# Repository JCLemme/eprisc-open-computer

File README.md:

# epRISC Open Computer
An open-source computer

# **THIS REPO IS DEPRECATED - check out the "eprisc", "snag", "spasm", and "flail" repositories instead**

---

## Building things
Right now, the system testbench and the assembler can be compiled. Just run the provided Makefiles in their respective directories.

To build the system testbench, you'll need make, Icarus Verilog, and ideally some sort of waveform viewer (like GTKWave). The testbench emulates all of the system's I/O devices, but they aren't connected to anything, so you'll have to read the output waveforms yourself and determine if they're correct or not for debugging. Another thing to pay attention to is the length of time the testbench runs for; running the emulation long enough to catch rare problems might generate VCD files of several hundred megabytes.

To build spasm, you'll need g++, make, and libboost. Everything's been updated for the v5 ISA.

## Developing software
You can use spasm and the system testbench to develop software for the epRISC system. Documentation isn't complete for the new parts of the assembler, but you can use the code in the software/rom/ directory as a starting point. The full list of assembly instructions are in the .cpu file in the software/toolchain/spasm/ directory. 

The assembler can generate binaries in big-endian format and Verilog arrays. Run spasm with the -t flag, replace the contents of the array in the firmware/core/rom_v1r0.v file with the output file generated by spasm, and make the system testbench as directed above. 

## Running on hardware
A Quartus project is provided in the firmware/core directory to run the CPU and its peripherals on an Altera MAX 10 FPGA. You should be able, with little modification, to get the project to synthesize to another Altera FPGA or to another manufacturer's FPGA.

As of 04-05-2017, the computer is running successfully on its development board. If you're interested in running the system on your hardware, please contact me.

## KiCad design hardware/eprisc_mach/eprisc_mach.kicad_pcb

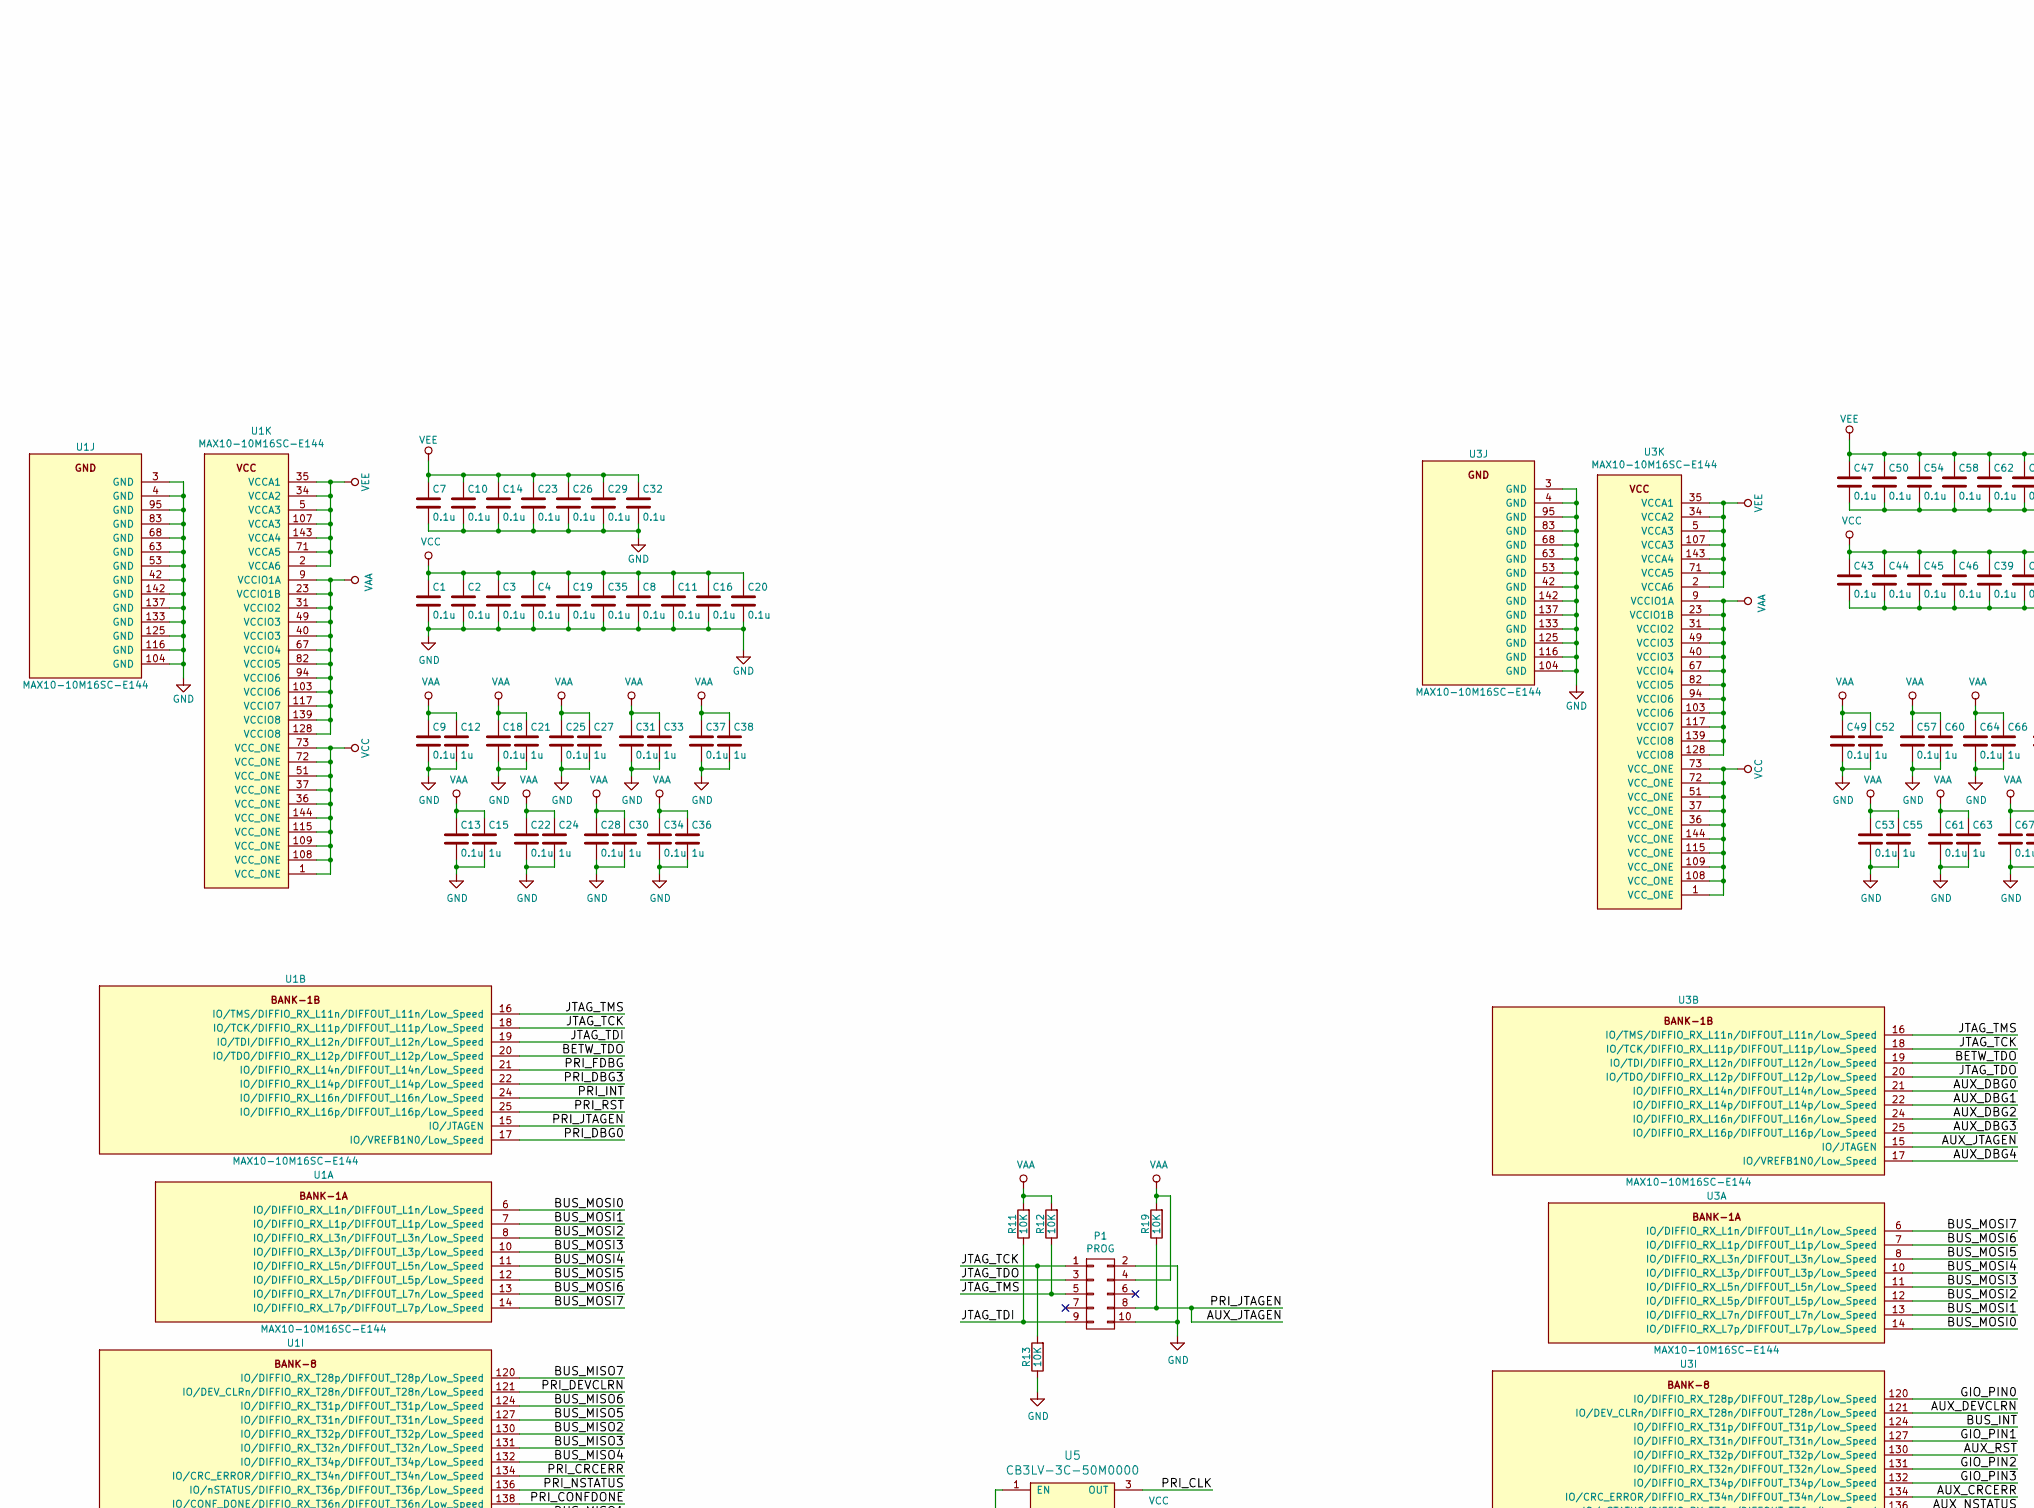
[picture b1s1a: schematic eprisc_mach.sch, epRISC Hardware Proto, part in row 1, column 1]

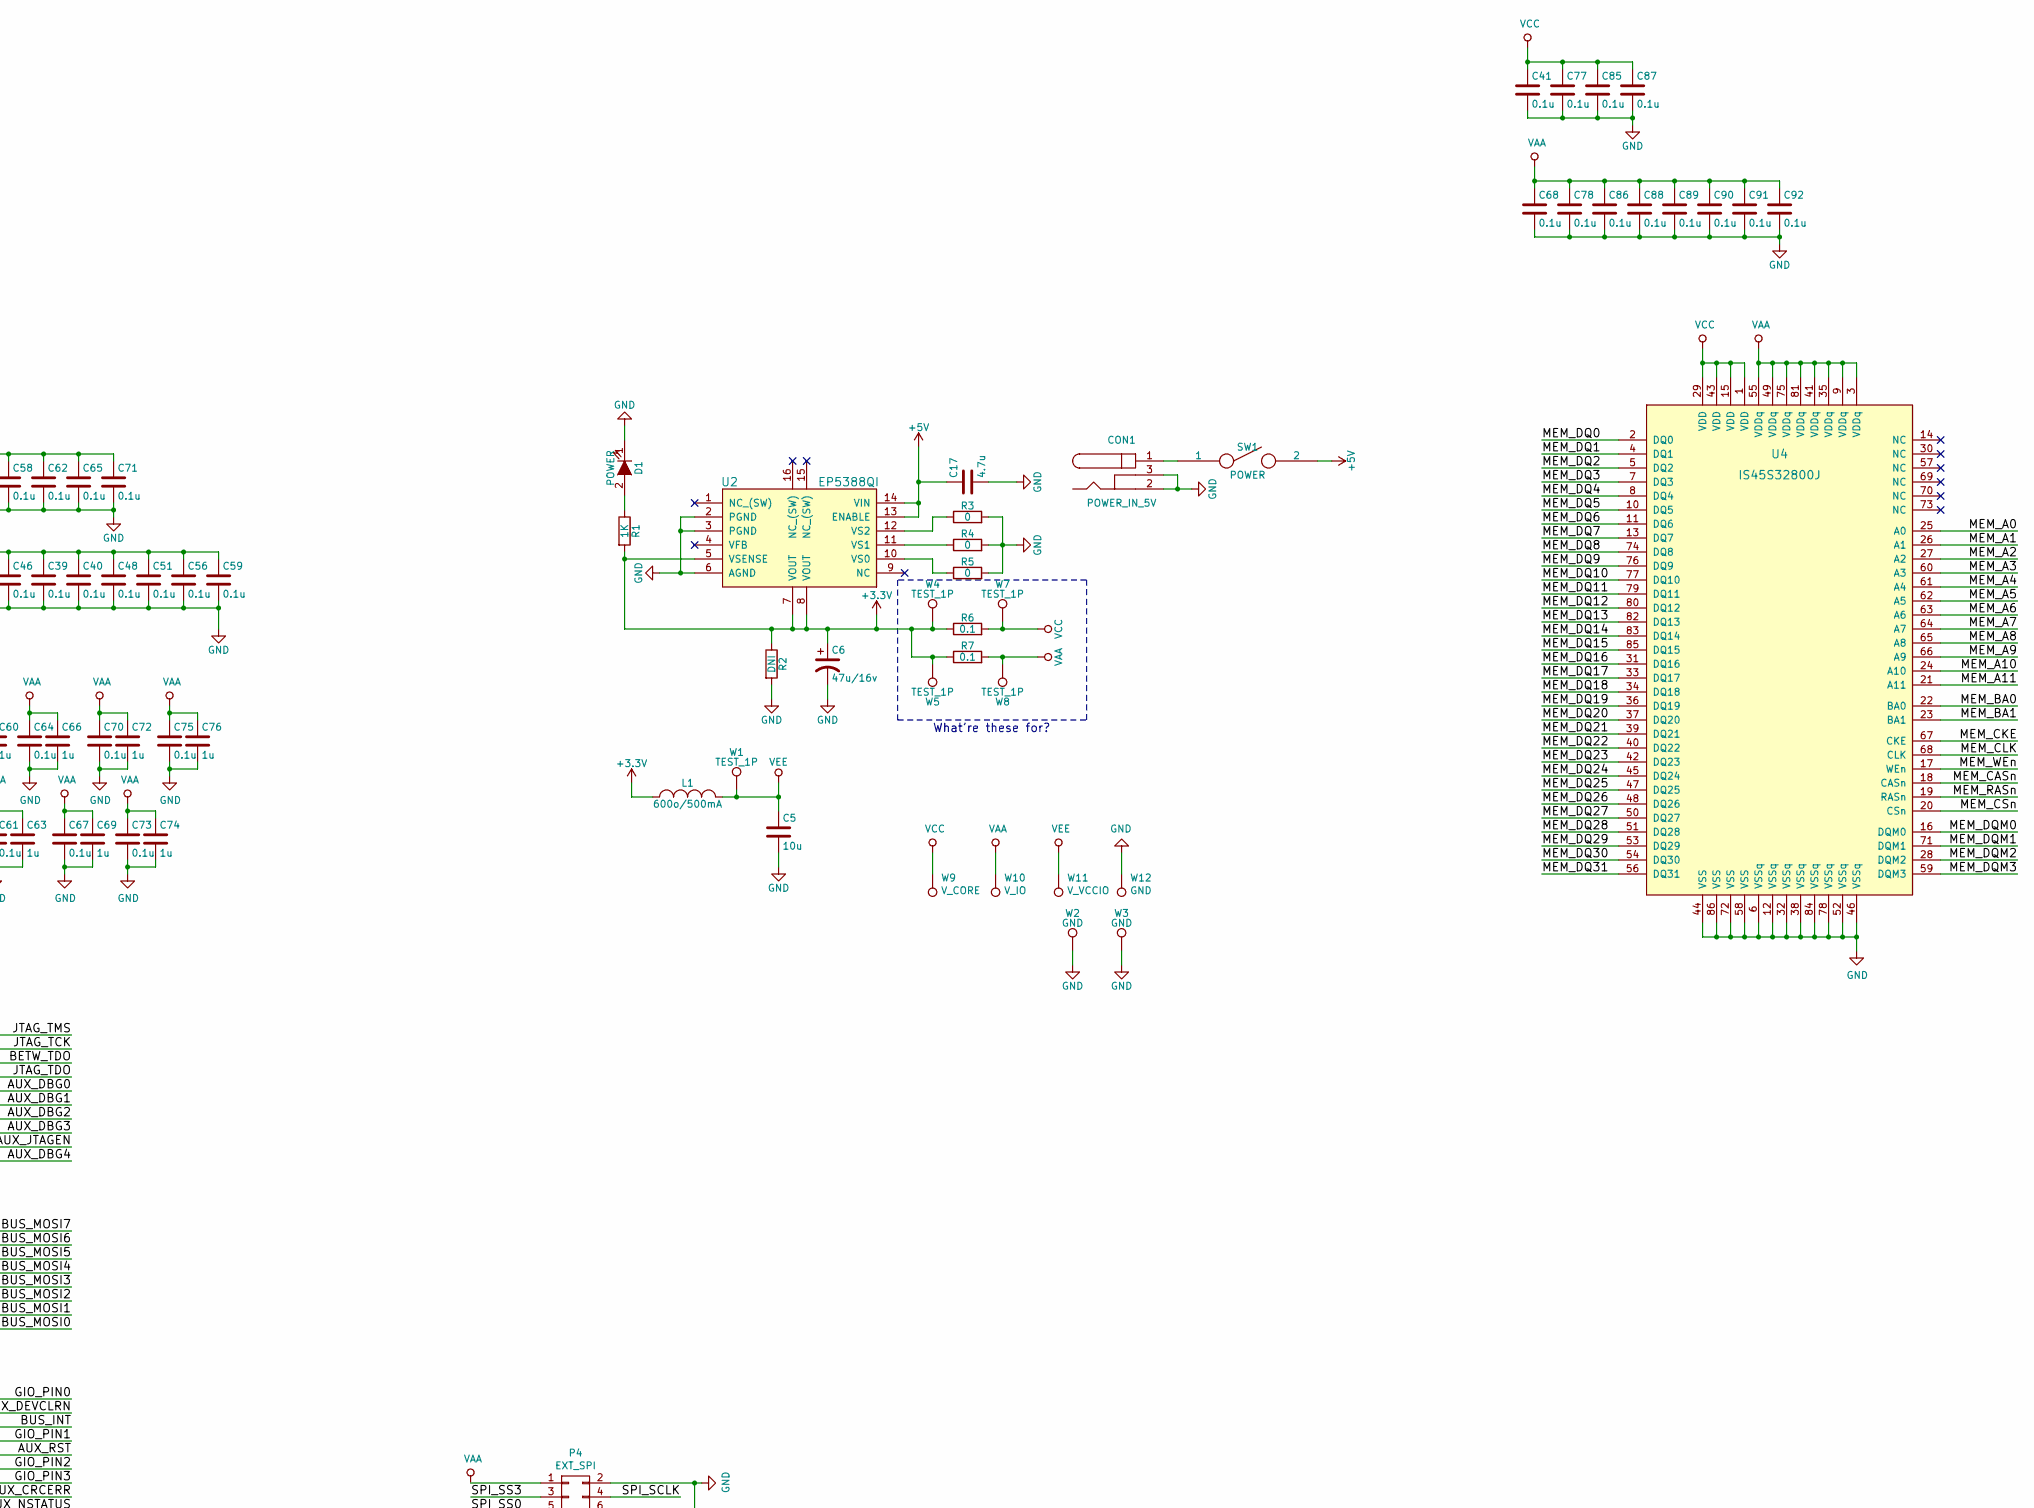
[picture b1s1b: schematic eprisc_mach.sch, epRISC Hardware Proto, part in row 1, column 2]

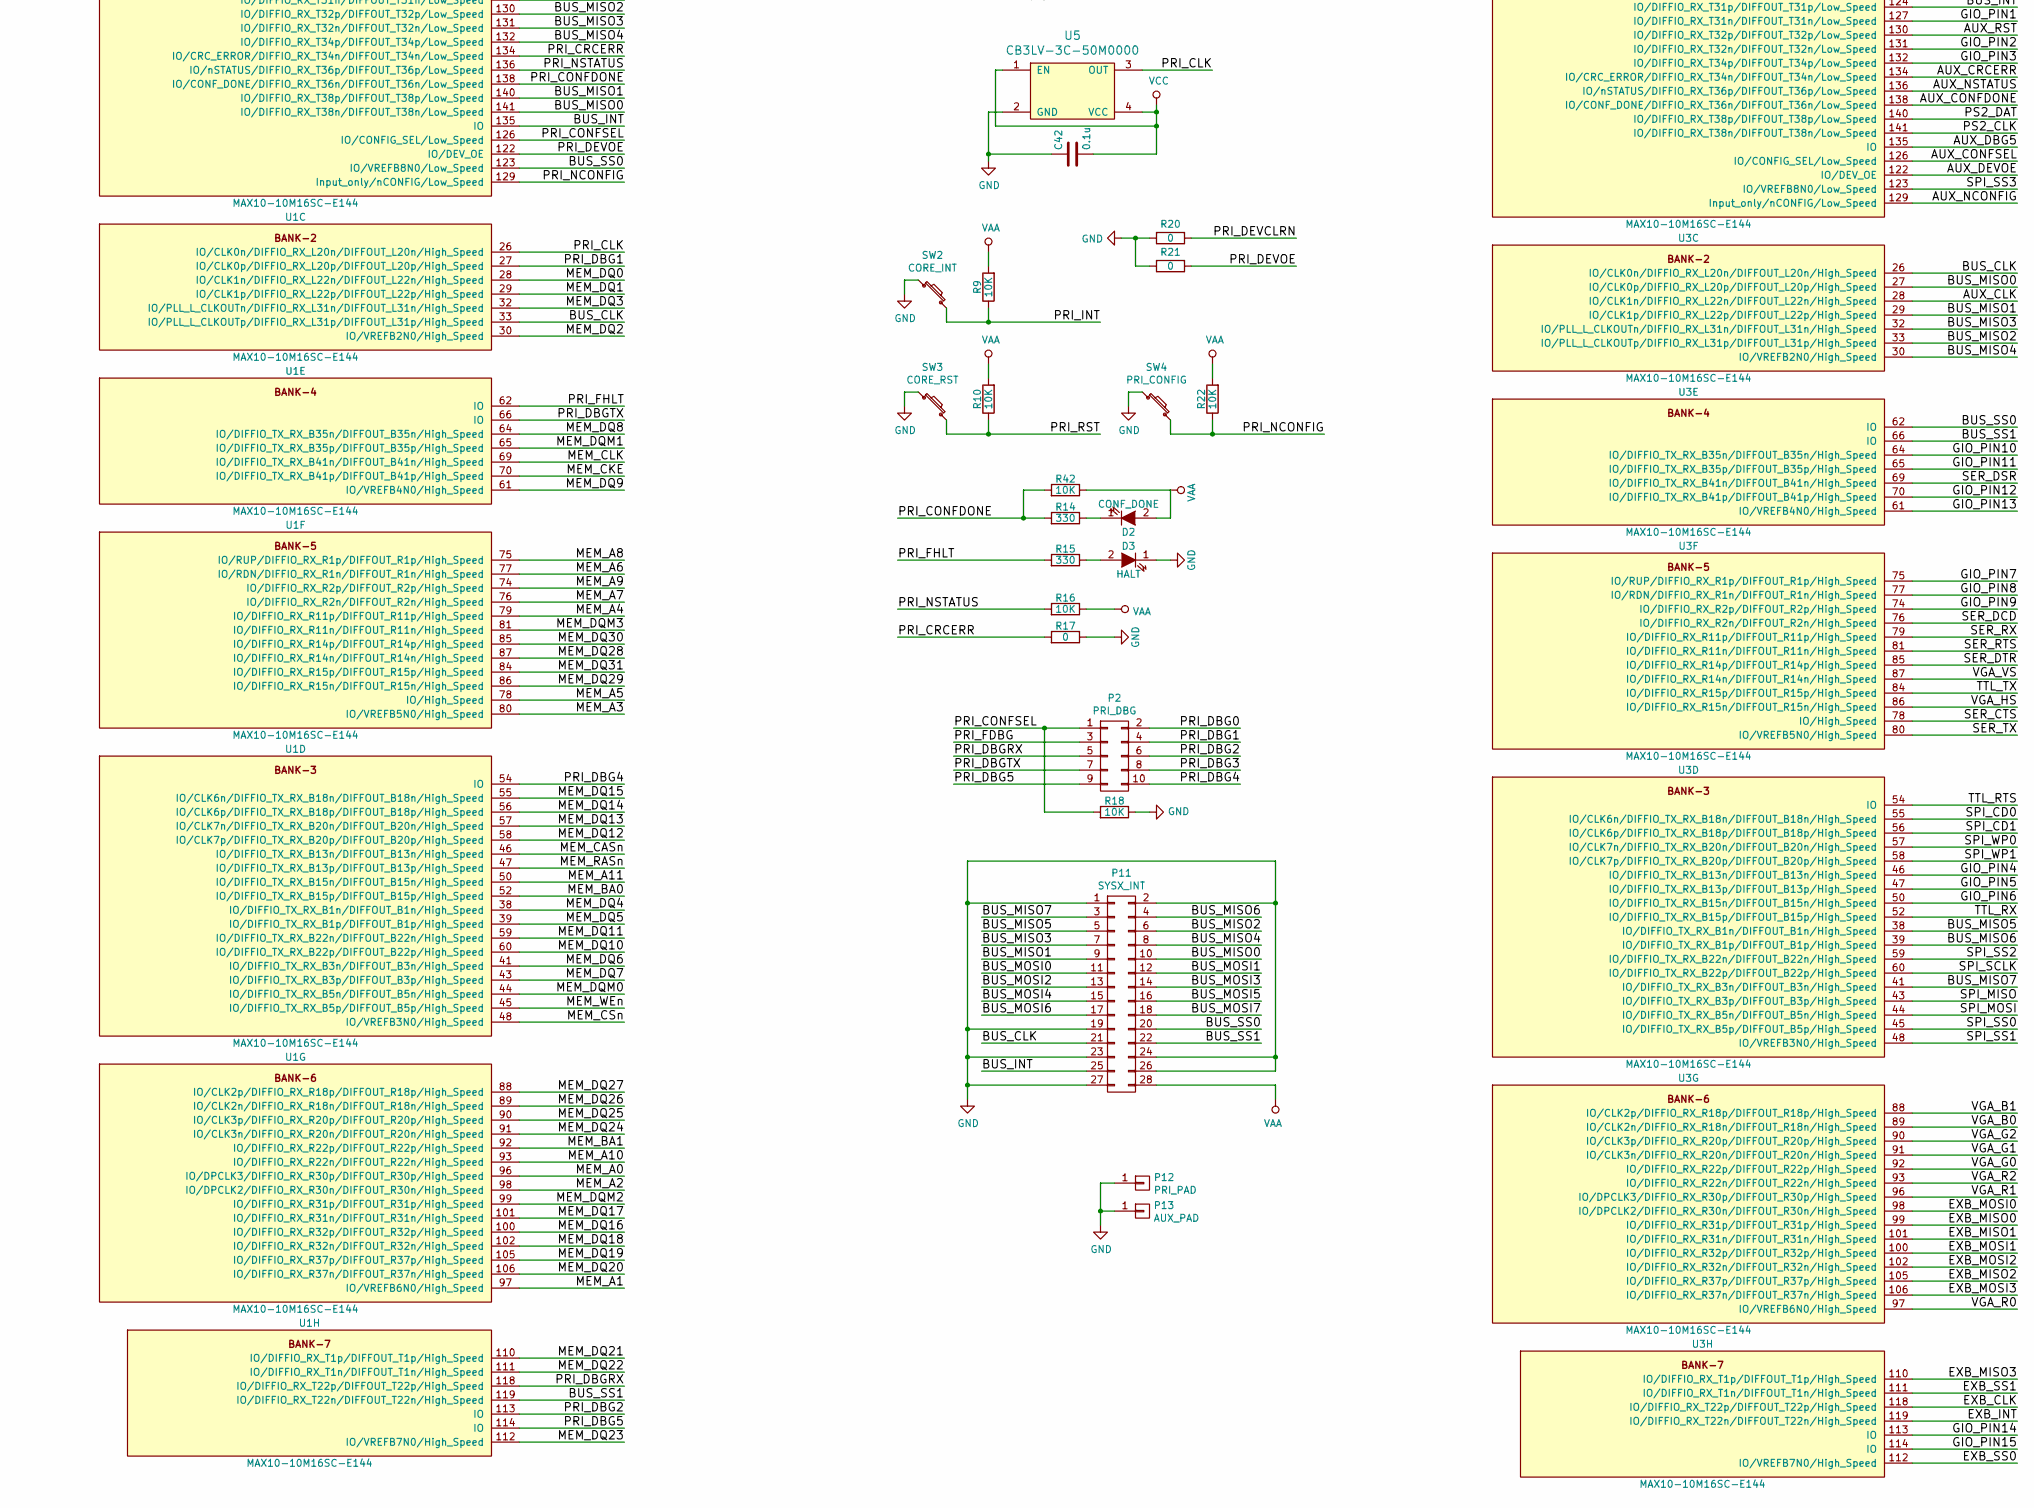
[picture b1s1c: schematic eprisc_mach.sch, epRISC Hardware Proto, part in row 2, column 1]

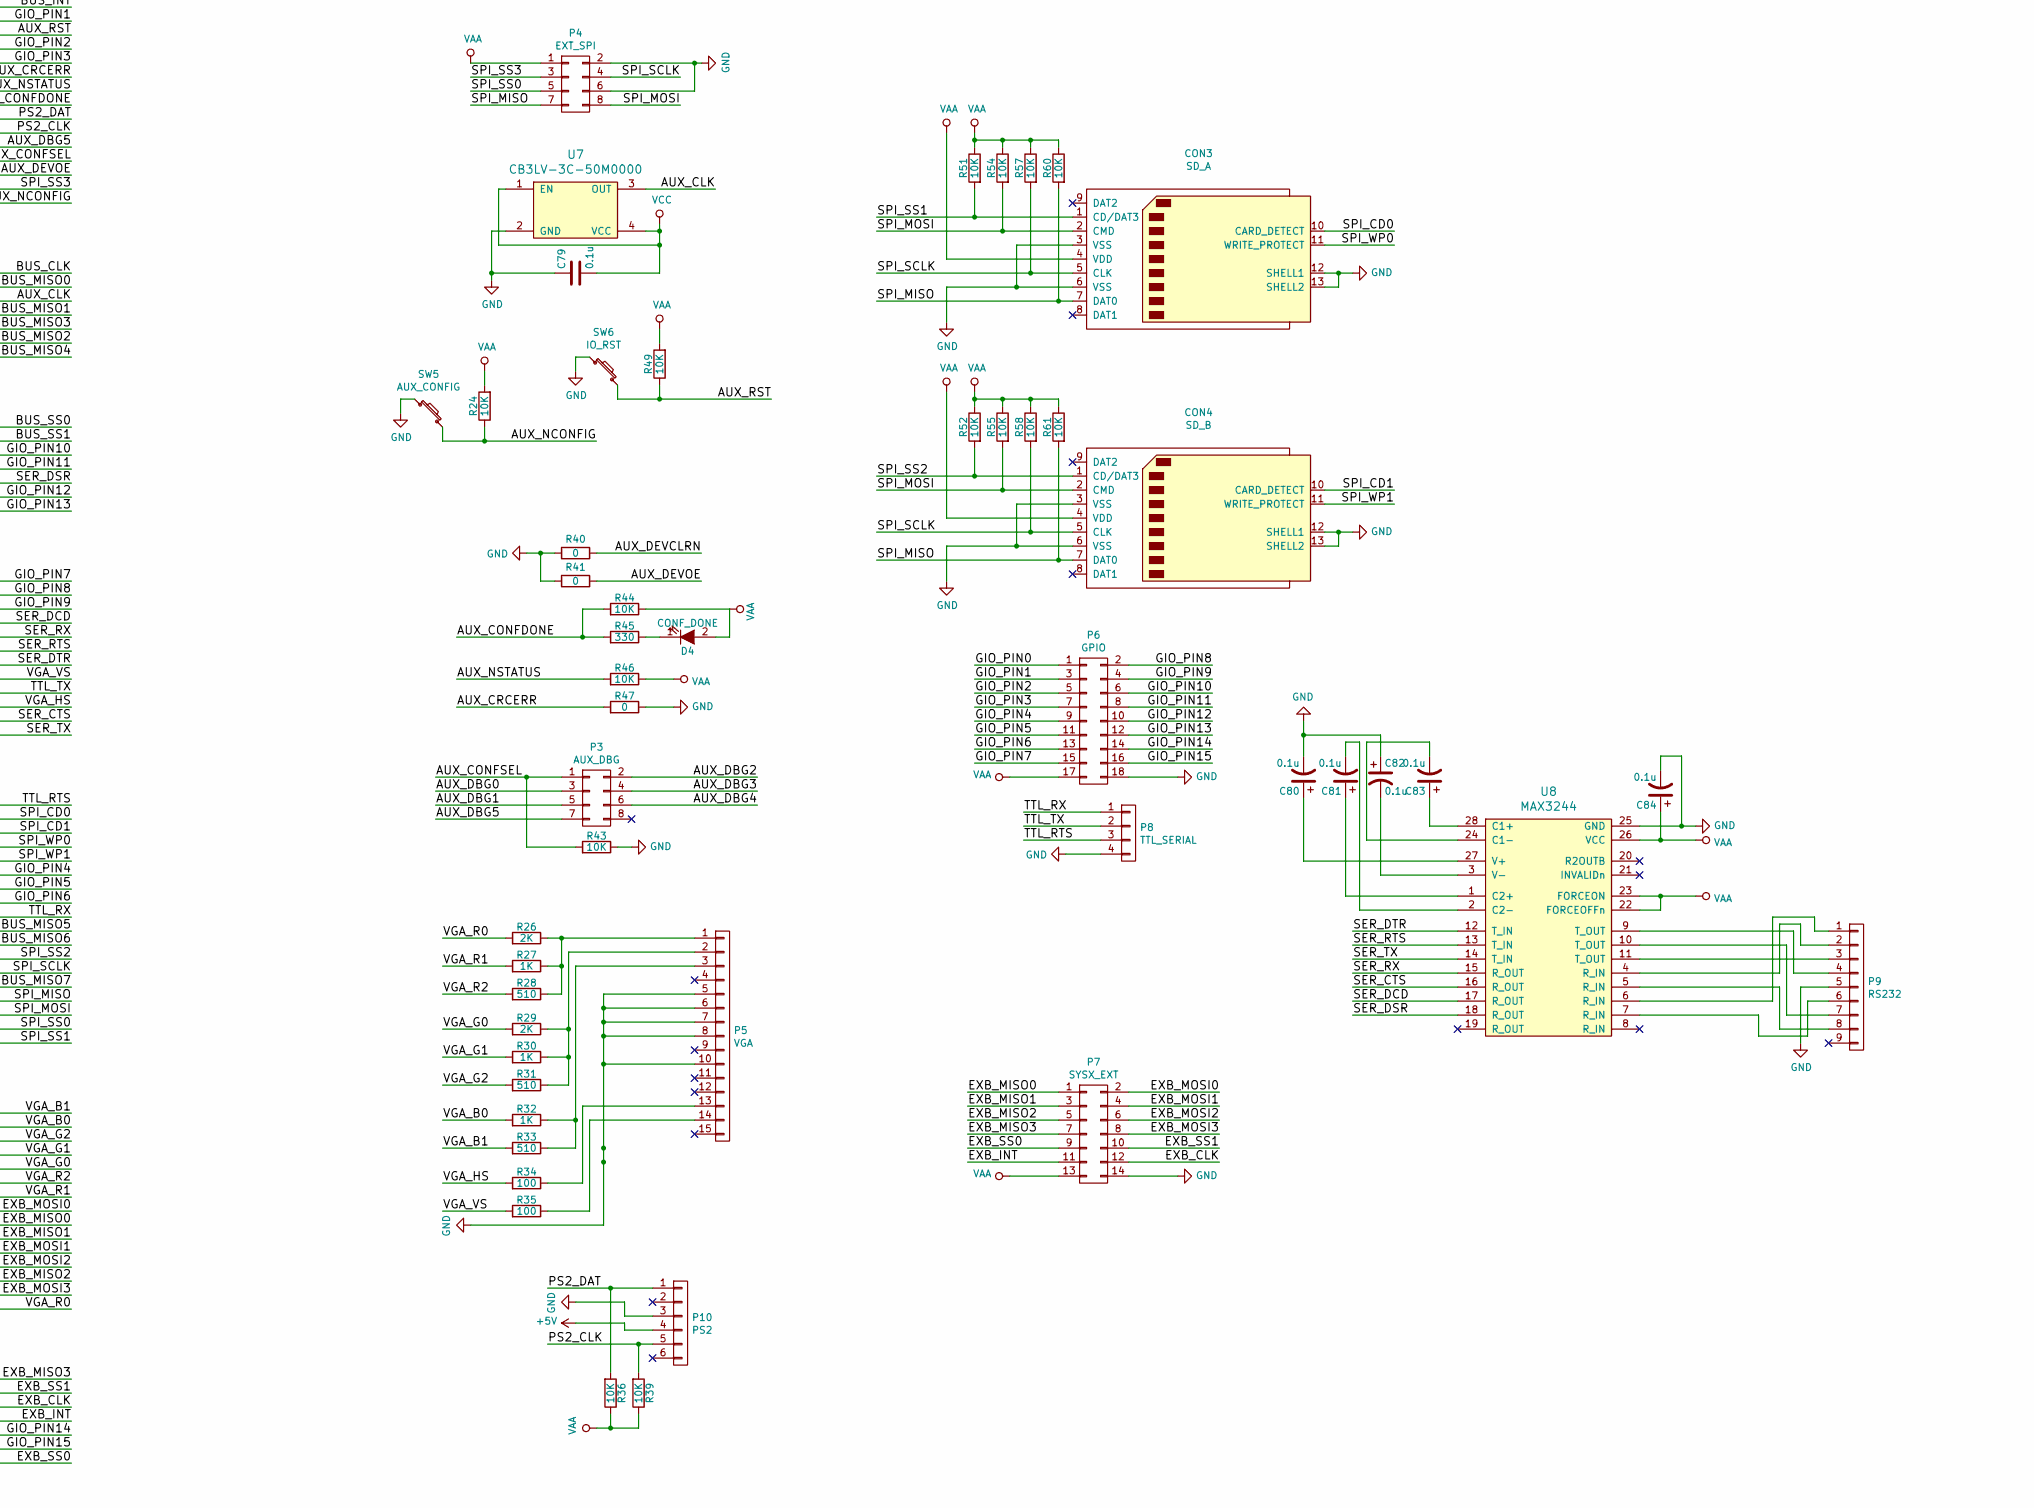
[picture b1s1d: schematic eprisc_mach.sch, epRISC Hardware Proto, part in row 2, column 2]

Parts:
C1, C2, C3, C4, C7, C8, C9, C10, C11, C13, C14, C16, C18, C19, C20, C22, C23, C25, C26, C28, C29, C31, C32, C34, C35, C37, C39, C40, C41, C42, C43, C44, C45, C46, C47, C48, C49, C50, C51, C53, C54, C56, C57, C58, C59, C61, C62, C64, C65, C67, C68, C70, C71, C73, C75, C77, C78, C79, C80, C81, C82, C83, C84, C85, C86, C87, C88, C89, C90, C91, C92: 0.1u; C_0805
C5: 10u; C_0805
C6: 47u/16v; C_0805
C12, C15, C21, C24, C27, C30, C33, C36, C38, C52, C55, C60, C63, C66, C69, C72, C74, C76: 1u; C_0805
C17: 4.7u; C_0805
CON1: POWER_IN_5V; BARREL_JACK
CON3: SD_A; SD_Card_Receptacle
CON4: SD_B; SD_Card_Receptacle
D1: POWER; LED_0805
D2, D4: CONF_DONE; LED_0805
D3: HALT; LED_0805
L1: 600o/500mA; inductor_smd_0603
P1: PROG; Pin_Header_Straight_2x05
P2: PRI_DBG; SMD_STRIP_10
P3: AUX_DBG; SMD_STRIP_8
P4: EXT_SPI; Socket_Strip_Angled_2x04
P5: VGA; DB15F-VGA-AMP
P6: GPIO; Socket_Strip_Angled_2x09
P7: SYSX_EXT; Socket_Strip_Angled_2x07
P8: TTL_SERIAL; Socket_Strip_Straight_1x04
P9: RS232; DB_9F
P10: PS2; 00JG-MiniDin6
P11: SYSX_INT; SMD_STRIP_28
P12: PRI_PAD; MountingHole_2.5mm_Pad
P13: AUX_PAD; MountingHole_2.5mm_Pad
R1, R27, R30, R32: 1K; R_0805
R2: DNI; R_0805
R3, R4, R5, R17, R20, R21, R40, R41, R47: 0; R_0805
R6, R7: 0.1; R_0805
R9, R10, R11, R12, R13, R16, R18, R19, R22, R24, R36, R39, R42, R43, R44, R46, R49, R51, R52, R54, R55, R57, R58, R60, R61: 10K; R_0805
R14, R15, R45: 330; R_0805
R26, R29: 2K; R_0805
R28, R31, R33: 510; R_0805
R34, R35: 100; R_0805
SW1: POWER; SW_SLIDE_PWR
SW2: CORE_INT; SW_PUSH_SMALL
SW3: CORE_RST; SW_PUSH_SMALL
SW4: PRI_CONFIG; SW_PUSH_SMALL
SW5: AUX_CONFIG; SW_PUSH_SMALL
SW6: IO_RST; SW_PUSH_SMALL
U1, U3: MAX10-10M16SC-E144; LQFP-144_20x20mm_Pitch0.5mm
U2: EP5388QI; QFN-16-ALTERA
U4: IS45S32800J; TSOP-86
U5, U7: CB3LV-3C-50M0000; CRYSTAL_CTS
U8: MAX3244; SSOP-28_5.3x10.2mm_Pitch0.65mm
W1, W4, W5, W7, W8: TEST_1P; Measurement_Point_Round-SMD-Pad_Small
W2, W3, W12: GND; Measurement_Point_Round-SMD-Pad_Small
W9: V_CORE; Measurement_Point_Round-SMD-Pad_Small
W10: V_IO; Measurement_Point_Round-SMD-Pad_Small
W11: V_VCCIO; Measurement_Point_Round-SMD-Pad_Small

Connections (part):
+3V3: C6.1, L1.1, R1.2, R2.1, R6.1, R7.1, U2.5 (VSENSE), U2.7 (VOUT), U2.8 (VOUT), W4.1, W5.1
+5V: C17.1, P10.4, SW1.2, U2.13 (ENABLE), U2.14 (VIN)
/AUX_CLK: U3.28 (IO/CLK1n/DIFFIO_RX_L22n/DIFFOUT_L22n/Hi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), U7.3 (OUT)
/AUX_CONFDONE: R44.2, R45.2, U3.138 (IO/CONF_DONE/DIFFIO_RX_T36n/DIFFOUT_T36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)
/AUX_CONFSEL: P3.1, R43.2, U3.126 (IO/CONFIG_SEL/Low_Speed)
/AUX_CRCERR: R47.2, U3.134 (IO/CRC_ERROR/DIFFIO_RX_T34n/DIFFOUT_T34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)
/AUX_DBG0: P3.3, U3.21 (IO/DIFFIO_RX_L14n/DIFFOUT_L14n/Low_Speed)
/AUX_DBG1: P3.5, U3.22 (IO/DIFFIO_RX_L14p/DIFFOUT_L14p/Low_Speed)
/AUX_DBG2: P3.2, U3.24 (IO/DIFFIO_RX_L16n/DIFFOUT_L16n/Low_Speed)
/AUX_DBG3: P3.4, U3.25 (IO/DIFFIO_RX_L16p/DIFFOUT_L16p/Low_Speed)
/AUX_DBG4: P3.6, U3.17 (IO/VREFB1N0/Low_Speed)
/AUX_DBG5: P3.7, U3.135 (IO)
/AUX_DEVCLRN: R40.1, U3.121 (IO/DEV_CLRn/DIFFIO_RX_T28n/DIFFOUT_T28n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)
/AUX_DEVOE: R41.1, U3.122 (IO/DEV_OE)
/AUX_JTAGEN: P1.8, R19.1, U1.15 (IO/JTAGEN), U3.15 (IO/JTAGEN)
/AUX_NCONFIG: R24.1, SW5.2, U3.129 (Input_only/nCONFIG/Low_Speed)
/AUX_NSTATUS: R46.2, U3.136 (IO/nSTATUS/DIFFIO_RX_T36p/DIFFOUT_T36p/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)
/AUX_RST: R49.1, SW6.2, U3.130 (IO/DIFFIO_RX_T32p/DIFFOUT_T32p/Low_Speed)
/BETW_TDO: U1.20 (IO/TDO/DIFFIO_RX_L12p/DIFFOUT_L12p/Low_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), U3.19 (IO/TDI/DIFFIO_RX_L12n/DIFFOUT_L12n/Low_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)
/BUS_CLK: P11.21, U1.33 (IO/PLL_L_CLKOUTp/DIFFIO_RX_L31p/DIFFOUT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), U3.26 (IO/CLK0n/DIFFIO_RX_L20n/DIFFOUT_L20n/Hi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)
/BUS_INT: P11.25, U1.135 (IO), U3.124 (IO/DIFFIO_RX_T31p/DIFFOUT_T31p/Low_Speed)
/BUS_MISO0: P11.10, U1.141 (IO/DIFFIO_RX_T38n/DIFFOUT_T38n/Low_Speed), U3.27 (IO/CLK0p/DIFFIO_RX_L20p/DIFFOUT_L20p/Hi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)
/BUS_MISO1: P11.9, U1.140 (IO/DIFFIO_RX_T38p/DIFFOUT_T38p/Low_Speed), U3.29 (IO/CLK1p/DIFFIO_RX_L22p/DIFFOUT_L22p/Hi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)
/BUS_MISO2: P11.6, U1.130 (IO/DIFFIO_RX_T32p/DIFFOUT_T32p/Low_Speed), U3.33 (IO/PLL_L_CLKOUTp/DIFFIO_RX_L31p/DIFFOUT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)
/BUS_MISO3: P11.7, U1.131 (IO/DIFFIO_RX_T32n/DIFFOUT_T32n/Low_Speed), U3.32 (IO/PLL_L_CLKOUTn/DIFFIO_RX_L31n/DIFFOUT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)
/BUS_MISO4: P11.8, U1.132 (IO/DIFFIO_RX_T34p/DIFFOUT_T34p/Low_Speed), U3.30 (IO/VREFB2N0/High_Speed)
/BUS_MISO5: P11.5, U1.127 (IO/DIFFIO_RX_T31n/DIFFOUT_T31n/Low_Speed), U3.38 (IO/DIFFIO_TX_RX_B1n/DIFFOUT_B1n/High_Sp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)
/BUS_MISO6: P11.4, U1.124 (IO/DIFFIO_RX_T31p/DIFFOUT_T31p/Low_Speed), U3.39 (IO/DIFFIO_TX_RX_B1p/DIFFOUT_B1p/High_Sp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)
/BUS_MISO7: P11.3, U1.120 (IO/DIFFIO_RX_T28p/DIFFOUT_T28p/Low_Speed), U3.41 (IO/DIFFIO_TX_RX_B3n/DIFFOUT_B3n/High_Sp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)
/BUS_MOSI0: P11.11, U1.6 (IO/DIFFIO_RX_L1n/DIFFOUT_L1n/Low_Speed), U3.14 (IO/DIFFIO_RX_L7p/DIFFOUT_L7p/Low_Speed)
/BUS_MOSI1: P11.12, U1.7 (IO/DIFFIO_RX_L1p/DIFFOUT_L1p/Low_Speed), U3.13 (IO/DIFFIO_RX_L7n/DIFFOUT_L7n/Low_Speed)
/BUS_MOSI2: P11.13, U1.8 (IO/DIFFIO_RX_L3n/DIFFOUT_L3n/Low_Speed), U3.12 (IO/DIFFIO_RX_L5p/DIFFOUT_L5p/Low_Speed)
/BUS_MOSI3: P11.14, U1.10 (IO/DIFFIO_RX_L3p/DIFFOUT_L3p/Low_Speed), U3.11 (IO/DIFFIO_RX_L5n/DIFFOUT_L5n/Low_Speed)
/BUS_MOSI4: P11.15, U1.11 (IO/DIFFIO_RX_L5n/DIFFOUT_L5n/Low_Speed), U3.10 (IO/DIFFIO_RX_L3p/DIFFOUT_L3p/Low_Speed)
/BUS_MOSI5: P11.16, U1.12 (IO/DIFFIO_RX_L5p/DIFFOUT_L5p/Low_Speed), U3.8 (IO/DIFFIO_RX_L3n/DIFFOUT_L3n/Low_Speed)
/BUS_MOSI6: P11.17, U1.13 (IO/DIFFIO_RX_L7n/DIFFOUT_L7n/Low_Speed), U3.7 (IO/DIFFIO_RX_L1p/DIFFOUT_L1p/Low_Speed)
/BUS_MOSI7: P11.18, U1.14 (IO/DIFFIO_RX_L7p/DIFFOUT_L7p/Low_Speed), U3.6 (IO/DIFFIO_RX_L1n/DIFFOUT_L1n/Low_Speed)
/BUS_SS0: P11.20, U1.123 (IO/VREFB8N0/Low_Speed), U3.62 (IO)
/BUS_SS1: P11.22, U1.119 (IO/DIFFIO_RX_T22n/DIFFOUT_T22n/High_Spe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), U3.66 (IO)
/EXB_CLK: P7.12, U3.118 (IO/DIFFIO_RX_T22p/DIFFOUT_T22p/High_Spe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)
/EXB_INT: P7.11, U3.119 (IO/DIFFIO_RX_T22n/DIFFOUT_T22n/High_Spe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)
/EXB_MISO0: P7.1, U3.99 (IO/DIFFIO_RX_R31p/DIFFOUT_R31p/High_Spe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)
/EXB_MISO1: P7.3, U3.101 (IO/DIFFIO_RX_R31n/DIFFOUT_R31n/High_Spe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)
/EXB_MISO2: P7.5, U3.105 (IO/DIFFIO_RX_R37p/DIFFOUT_R37p/High_Spe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)
/EXB_MISO3: P7.7, U3.110 (IO/DIFFIO_RX_T1p/DIFFOUT_T1p/High_Speed)
/EXB_MOSI0: P7.2, U3.98 (IO/DPCLK2/DIFFIO_RX_R30n/DIFFOUT_R30n/H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)
/EXB_MOSI1: P7.4, U3.100 (IO/DIFFIO_RX_R32p/DIFFOUT_R32p/High_Spe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)
/EXB_MOSI2: P7.6, U3.102 (IO/DIFFIO_RX_R32n/DIFFOUT_R32n/High_Spe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)
/EXB_MOSI3: P7.8, U3.106 (IO/DIFFIO_RX_R37n/DIFFOUT_R37n/High_Spe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)
/EXB_SS0: P7.9, U3.112 (IO/VREFB7N0/High_Speed)
/EXB_SS1: P7.10, U3.111 (IO/DIFFIO_RX_T1n/DIFFOUT_T1n/High_Speed)
/GIO_PIN0: P6.1, U3.120 (IO/DIFFIO_RX_T28p/DIFFOUT_T28p/Low_Speed)
/GIO_PIN1: P6.3, U3.127 (IO/DIFFIO_RX_T31n/DIFFOUT_T31n/Low_Speed)
/GIO_PIN2: P6.5, U3.131 (IO/DIFFIO_RX_T32n/DIFFOUT_T32n/Low_Speed)
/GIO_PIN3: P6.7, U3.132 (IO/DIFFIO_RX_T34p/DIFFOUT_T34p/Low_Speed)
/GIO_PIN4: P6.9, U3.46 (IO/DIFFIO_TX_RX_B13n/DIFFOUT_B13n/High_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)
/GIO_PIN5: P6.11, U3.47 (IO/DIFFIO_TX_RX_B13p/DIFFOUT_B13p/High_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)
/GIO_PIN6: P6.13, U3.50 (IO/DIFFIO_TX_RX_B15n/DIFFOUT_B15n/High_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)
/GIO_PIN7: P6.15, U3.75 (IO/RUP/DIFFIO_RX_R1p/DIFFOUT_R1p/High_S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)
/GIO_PIN8: P6.2, U3.77 (IO/RDN/DIFFIO_RX_R1n/DIFFOUT_R1n/High_S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)
/GIO_PIN9: P6.4, U3.74 (IO/DIFFIO_RX_R2p/DIFFOUT_R2p/High_Speed)
/GIO_PIN10: P6.6, U3.64 (IO/DIFFIO_TX_RX_B35n/DIFFOUT_B35n/High_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)
/GIO_PIN11: P6.8, U3.65 (IO/DIFFIO_TX_RX_B35p/DIFFOUT_B35p/High_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)
/GIO_PIN12: P6.10, U3.70 (IO/DIFFIO_TX_RX_B41p/DIFFOUT_B41p/High_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)
/GIO_PIN13: P6.12, U3.61 (IO/VREFB4N0/High_Speed)
/GIO_PIN14: P6.14, U3.113 (IO)
/GIO_PIN15: P6.16, U3.114 (IO)
/JTAG_TCK: P1.1, R13.2, U1.18 (IO/TCK/DIFFIO_RX_L11p/DIFFOUT_L11p/Low_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), U3.18 (IO/TCK/DIFFIO_RX_L11p/DIFFOUT_L11p/Low_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)
/JTAG_TDI: P1.9, R11.1, U1.19 (IO/TDI/DIFFIO_RX_L12n/DIFFOUT_L12n/Low_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)
/JTAG_TDO: P1.3, U3.20 (IO/TDO/DIFFIO_RX_L12p/DIFFOUT_L12p/Low_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)
/JTAG_TMS: P1.5, R12.1, U1.16 (IO/TMS/DIFFIO_RX_L11n/DIFFOUT_L11n/Low_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), U3.16 (IO/TMS/DIFFIO_RX_L11n/DIFFOUT_L11n/Low_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)
/MEM_A0: U1.96 (IO/DPCLK3/DIFFIO_RX_R30p/DIFFOUT_R30p/H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), U4.25 (A0)
/MEM_A1: U1.97 (IO/VREFB6N0/High_Speed), U4.26 (A1)
/MEM_A2: U1.98 (IO/DPCLK2/DIFFIO_RX_R30n/DIFFOUT_R30n/H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), U4.27 (A2)
/MEM_A3: U1.80 (IO/VREFB5N0/High_Speed), U4.60 (A3)
/MEM_A4: U1.79 (IO/DIFFIO_RX_R11p/DIFFOUT_R11p/High_Spe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), U4.61 (A4)
/MEM_A5: U1.78 (IO/High_Speed), U4.62 (A5)
/MEM_A6: U1.77 (IO/RDN/DIFFIO_RX_R1n/DIFFOUT_R1n/High_S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), U4.63 (A6)
/MEM_A7: U1.76 (IO/DIFFIO_RX_R2n/DIFFOUT_R2n/High_Speed), U4.64 (A7)
/MEM_A8: U1.75 (IO/RUP/DIFFIO_RX_R1p/DIFFOUT_R1p/High_S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), U4.65 (A8)
/MEM_A9: U1.74 (IO/DIFFIO_RX_R2p/DIFFOUT_R2p/High_Speed), U4.66 (A9)
/MEM_A10: U1.93 (IO/DIFFIO_RX_R22n/DIFFOUT_R22n/High_Spe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), U4.24 (A10)
/MEM_A11: U1.50 (IO/DIFFIO_TX_RX_B15n/DIFFOUT_B15n/High_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), U4.21 (A11)
/MEM_BA0: U1.52 (IO/DIFFIO_TX_RX_B15p/DIFFOUT_B15p/High_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), U4.22 (BA0)
/MEM_BA1: U1.92 (IO/DIFFIO_RX_R22p/DIFFOUT_R22p/High_Spe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), U4.23 (BA1)
/MEM_CASn: U1.46 (IO/DIFFIO_TX_RX_B13n/DIFFOUT_B13n/High_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), U4.18 (CASn)
/MEM_CKE: U1.70 (IO/DIFFIO_TX_RX_B41p/DIFFOUT_B41p/High_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), U4.67 (CKE)
/MEM_CLK: U1.69 (IO/DIFFIO_TX_RX_B41n/DIFFOUT_B41n/High_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), U4.68 (CLK)
/MEM_CSn: U1.48 (IO/VREFB3N0/High_Speed), U4.20 (CSn)
/MEM_DQ0: U1.28 (IO/CLK1n/DIFFIO_RX_L22n/DIFFOUT_L22n/Hi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), U4.2 (DQ0)
/MEM_DQ1: U1.29 (IO/CLK1p/DIFFIO_RX_L22p/DIFFOUT_L22p/Hi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), U4.4 (DQ1)
/MEM_DQ2: U1.30 (IO/VREFB2N0/High_Speed), U4.5 (DQ2)
/MEM_DQ3: U1.32 (IO/PLL_L_CLKOUTn/DIFFIO_RX_L31n/DIFFOUT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), U4.7 (DQ3)
/MEM_DQ4: U1.38 (IO/DIFFIO_TX_RX_B1n/DIFFOUT_B1n/High_Sp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), U4.8 (DQ4)
/MEM_DQ5: U1.39 (IO/DIFFIO_TX_RX_B1p/DIFFOUT_B1p/High_Sp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), U4.10 (DQ5)
/MEM_DQ6: U1.41 (IO/DIFFIO_TX_RX_B3n/DIFFOUT_B3n/High_Sp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), U4.11 (DQ6)
/MEM_DQ7: U1.43 (IO/DIFFIO_TX_RX_B3p/DIFFOUT_B3p/High_Sp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), U4.13 (DQ7)
/MEM_DQ8: U1.64 (IO/DIFFIO_TX_RX_B35n/DIFFOUT_B35n/High_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), U4.74 (DQ8)
/MEM_DQ9: U1.61 (IO/VREFB4N0/High_Speed), U4.76 (DQ9)
/MEM_DQ10: U1.60 (IO/DIFFIO_TX_RX_B22p/DIFFOUT_B22p/High_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), U4.77 (DQ10)
/MEM_DQ11: U1.59 (IO/DIFFIO_TX_RX_B22n/DIFFOUT_B22n/High_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), U4.79 (DQ11)
/MEM_DQ12: U1.58 (IO/CLK7p/DIFFIO_TX_RX_B20p/DIFFOUT_B20p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), U4.80 (DQ12)
/MEM_DQ13: U1.57 (IO/CLK7n/DIFFIO_TX_RX_B20n/DIFFOUT_B20n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), U4.82 (DQ13)
/MEM_DQ14: U1.56 (IO/CLK6p/DIFFIO_TX_RX_B18p/DIFFOUT_B18p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), U4.83 (DQ14)
/MEM_DQ15: U1.55 (IO/CLK6n/DIFFIO_TX_RX_B18n/DIFFOUT_B18n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), U4.85 (DQ15)
/MEM_DQ16: U1.100 (IO/DIFFIO_RX_R32p/DIFFOUT_R32p/High_Spe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), U4.31 (DQ16)
/MEM_DQ17: U1.101 (IO/DIFFIO_RX_R31n/DIFFOUT_R31n/High_Spe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), U4.33 (DQ17)
/MEM_DQ18: U1.102 (IO/DIFFIO_RX_R32n/DIFFOUT_R32n/High_Spe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), U4.34 (DQ18)
/MEM_DQ19: U1.105 (IO/DIFFIO_RX_R37p/DIFFOUT_R37p/High_Spe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), U4.36 (DQ19)
/MEM_DQ20: U1.106 (IO/DIFFIO_RX_R37n/DIFFOUT_R37n/High_Spe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), U4.37 (DQ20)
/MEM_DQ21: U1.110 (IO/DIFFIO_RX_T1p/DIFFOUT_T1p/High_Speed), U4.39 (DQ21)
/MEM_DQ22: U1.111 (IO/DIFFIO_RX_T1n/DIFFOUT_T1n/High_Speed), U4.40 (DQ22)
/MEM_DQ23: U1.112 (IO/VREFB7N0/High_Speed), U4.42 (DQ23)
/MEM_DQ24: U1.91 (IO/CLK3n/DIFFIO_RX_R20n/DIFFOUT_R20n/Hi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), U4.45 (DQ24)
/MEM_DQ25: U1.90 (IO/CLK3p/DIFFIO_RX_R20p/DIFFOUT_R20p/Hi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), U4.47 (DQ25)
/MEM_DQ26: U1.89 (IO/CLK2n/DIFFIO_RX_R18n/DIFFOUT_R18n/Hi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), U4.48 (DQ26)
/MEM_DQ27: U1.88 (IO/CLK2p/DIFFIO_RX_R18p/DIFFOUT_R18p/Hi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), U4.50 (DQ27)
/MEM_DQ28: U1.87 (IO/DIFFIO_RX_R14n/DIFFOUT_R14n/High_Spe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), U4.51 (DQ28)
/MEM_DQ29: U1.86 (IO/DIFFIO_RX_R15n/DIFFOUT_R15n/High_Spe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), U4.53 (DQ29)
/MEM_DQ30: U1.85 (IO/DIFFIO_RX_R14p/DIFFOUT_R14p/High_Spe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), U4.54 (DQ30)
/MEM_DQ31: U1.84 (IO/DIFFIO_RX_R15p/DIFFOUT_R15p/High_Spe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), U4.56 (DQ31)
/MEM_DQM0: U1.44 (IO/DIFFIO_TX_RX_B5n/DIFFOUT_B5n/High_Sp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), U4.16 (DQM0)
/MEM_DQM1: U1.65 (IO/DIFFIO_TX_RX_B35p/DIFFOUT_B35p/High_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), U4.71 (DQM1)
/MEM_DQM2: U1.99 (IO/DIFFIO_RX_R31p/DIFFOUT_R31p/High_Spe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), U4.28 (DQM2)
/MEM_DQM3: U1.81 (IO/DIFFIO_RX_R11n/DIFFOUT_R11n/High_Spe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), U4.59 (DQM3)
/MEM_RASn: U1.47 (IO/DIFFIO_TX_RX_B13p/DIFFOUT_B13p/High_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), U4.19 (RASn)
/MEM_WEn: U1.45 (IO/DIFFIO_TX_RX_B5p/DIFFOUT_B5p/High_Sp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), U4.17 (WEn)
/PRI_CLK: U1.26 (IO/CLK0n/DIFFIO_RX_L20n/DIFFOUT_L20n/Hi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), U5.3 (OUT)
/PRI_CONFDONE: R14.2, R42.2, U1.138 (IO/CONF_DONE/DIFFIO_RX_T36n/DIFFOUT_T36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)
/PRI_CONFSEL: P2.1, R18.2, U1.126 (IO/CONFIG_SEL/Low_Speed)
/PRI_CRCERR: R17.2, U1.134 (IO/CRC_ERROR/DIFFIO_RX_T34n/DIFFOUT_T34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)
/PRI_DBG0: P2.2, U1.17 (IO/VREFB1N0/Low_Speed)
/PRI_DBG1: P2.4, U1.27 (IO/CLK0p/DIFFIO_RX_L20p/DIFFOUT_L20p/Hi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)
/PRI_DBG2: P2.6, U1.113 (IO)
/PRI_DBG3: P2.8, U1.22 (IO/DIFFIO_RX_L14p/DIFFOUT_L14p/Low_Speed)
/PRI_DBG4: P2.10, U1.54 (IO)
/PRI_DBG5: P2.9, U1.114 (IO)
/PRI_DBGRX: P2.5, U1.118 (IO/DIFFIO_RX_T22p/DIFFOUT_T22p/High_Spe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)
/PRI_DBGTX: P2.7, U1.66 (IO)
/PRI_DEVCLRN: R20.1, U1.121 (IO/DEV_CLRn/DIFFIO_RX_T28n/DIFFOUT_T28n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)
/PRI_DEVOE: R21.1, U1.122 (IO/DEV_OE)
/PRI_FDBG: P2.3, U1.21 (IO/DIFFIO_RX_L14n/DIFFOUT_L14n/Low_Speed)
/PRI_FHLT: R15.2, U1.62 (IO)
/PRI_INT: R9.1, SW2.2, U1.24 (IO/DIFFIO_RX_L16n/DIFFOUT_L16n/Low_Speed)
/PRI_NCONFIG: R22.1, SW4.2, U1.129 (Input_only/nCONFIG/Low_Speed)
/PRI_NSTATUS: R16.2, U1.136 (IO/nSTATUS/DIFFIO_RX_T36p/DIFFOUT_T36p/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)
/PRI_RST: R10.1, SW3.2, U1.25 (IO/DIFFIO_RX_L16p/DIFFOUT_L16p/Low_Speed)
/PS2_CLK: P10.5, R39.2, U3.141 (IO/DIFFIO_RX_T38n/DIFFOUT_T38n/Low_Speed)
/PS2_DAT: P10.1, R36.2, U3.140 (IO/DIFFIO_RX_T38p/DIFFOUT_T38p/Low_Speed)
/SER_CTS: U3.78 (IO/High_Speed), U8.16 (R_OUT)
/SER_DCD: U3.76 (IO/DIFFIO_RX_R2n/DIFFOUT_R2n/High_Speed), U8.17 (R_OUT)
/SER_DSR: U3.69 (IO/DIFFIO_TX_RX_B41n/DIFFOUT_B41n/High_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), U8.18 (R_OUT)
/SER_DTR: U3.85 (IO/DIFFIO_RX_R14p/DIFFOUT_R14p/High_Spe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), U8.12 (T_IN)
/SER_RTS: U3.81 (IO/DIFFIO_RX_R11n/DIFFOUT_R11n/High_Spe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), U8.13 (T_IN)
/SER_RX: U3.79 (IO/DIFFIO_RX_R11p/DIFFOUT_R11p/High_Spe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), U8.15 (R_OUT)
/SER_TX: U3.80 (IO/VREFB5N0/High_Speed), U8.14 (T_IN)
/SPI_CD0: CON3.10 (CARD_DETECT), U3.55 (IO/CLK6n/DIFFIO_TX_RX_B18n/DIFFOUT_B18n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)
/SPI_CD1: CON4.10 (CARD_DETECT), U3.56 (IO/CLK6p/DIFFIO_TX_RX_B18p/DIFFOUT_B18p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)
/SPI_MISO: CON3.7 (DAT0), CON4.7 (DAT0), P4.7, R60.2, R61.2, U3.43 (IO/DIFFIO_TX_RX_B3p/DIFFOUT_B3p/High_Sp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)
/SPI_MOSI: CON3.2 (CMD), CON4.2 (CMD), P4.8, R54.2, R55.2, U3.44 (IO/DIFFIO_TX_RX_B5n/DIFFOUT_B5n/High_Sp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)
/SPI_SCLK: CON3.5 (CLK), CON4.5 (CLK), P4.4, R57.2, R58.2, U3.60 (IO/DIFFIO_TX_RX_B22p/DIFFOUT_B22p/High_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)
/SPI_SS0: P4.5, U3.45 (IO/DIFFIO_TX_RX_B5p/DIFFOUT_B5p/High_Sp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)
/SPI_SS1: CON3.1 (CD/DAT3), R51.2, U3.48 (IO/VREFB3N0/High_Speed)
/SPI_SS2: CON4.1 (CD/DAT3), R52.2, U3.59 (IO/DIFFIO_TX_RX_B22n/DIFFOUT_B22n/High_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)
/SPI_SS3: P4.3, U3.123 (IO/VREFB8N0/Low_Speed)
/SPI_WP0: CON3.11 (WRITE_PROTECT), U3.57 (IO/CLK7n/DIFFIO_TX_RX_B20n/DIFFOUT_B20n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)
/SPI_WP1: CON4.11 (WRITE_PROTECT), U3.58 (IO/CLK7p/DIFFIO_TX_RX_B20p/DIFFOUT_B20p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)
/TTL_RTS: P8.3, U3.54 (IO)
/TTL_RX: P8.1, U3.52 (IO/DIFFIO_TX_RX_B15p/DIFFOUT_B15p/High_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)
/TTL_TX: P8.2, U3.84 (IO/DIFFIO_RX_R15p/DIFFOUT_R15p/High_Spe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)
/VGA_B0: R32.2, U3.89 (IO/CLK2n/DIFFIO_RX_R18n/DIFFOUT_R18n/Hi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)
/VGA_B1: R33.2, U3.88 (IO/CLK2p/DIFFIO_RX_R18p/DIFFOUT_R18p/Hi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)
/VGA_G0: R29.2, U3.92 (IO/DIFFIO_RX_R22p/DIFFOUT_R22p/High_Spe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)
/VGA_G1: R30.2, U3.91 (IO/CLK3n/DIFFIO_RX_R20n/DIFFOUT_R20n/Hi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)
/VGA_G2: R31.2, U3.90 (IO/CLK3p/DIFFIO_RX_R20p/DIFFOUT_R20p/Hi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)
/VGA_HS: R34.2, U3.86 (IO/DIFFIO_RX_R15n/DIFFOUT_R15n/High_Spe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)
/VGA_R0: R26.2, U3.97 (IO/VREFB6N0/High_Speed)
/VGA_R1: R27.2, U3.96 (IO/DPCLK3/DIFFIO_RX_R30p/DIFFOUT_R30p/H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)
/VGA_R2: R28.2, U3.93 (IO/DIFFIO_RX_R22n/DIFFOUT_R22n/High_Spe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)
/VGA_VS: R35.2, U3.87 (IO/DIFFIO_RX_R14n/DIFFOUT_R14n/High_Spe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)
GND: C1.2, C2.2, C3.2, C4.2, C5.2, C6.2, C7.2, C8.2, C9.2, C10.2, C11.2, C12.2, C13.2, C14.2, C15.2, C16.2, C17.2, C18.2, C19.2, C20.2, C21.2, C22.2, C23.2, C24.2, C25.2, C26.2, C27.2, C28.2, C29.2, C30.2, C31.2, C32.2, C33.2, C34.2, C35.2, C36.2, C37.2, C38.2, C39.2, C40.2, C41.2, C42.1, C43.2, C44.2, C45.2, C46.2, C47.2, C48.2, C49.2, C50.2, C51.2, C52.2, C53.2, C54.2, C55.2, C56.2, C57.2, C58.2, C59.2, C60.2, C61.2, C62.2, C63.2, C64.2, C65.2, C66.2, C67.2, C68.2, C69.2, C70.2, C71.2, C72.2, C73.2, C74.2, C75.2, C76.2, C77.2, C78.2, C79.1, C80.2, C82.1, C84.2, C85.2, C86.2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
unnamed: C80.1, U8.27 (V+)
unnamed: C81.1, U8.1 (C2+)
unnamed: C81.2, U8.2 (C2-)
unnamed: C82.2, U8.3 (V-)
unnamed: C83.1, U8.28 (C1+)
unnamed: C83.2, U8.24 (C1-)
unnamed: CON1.1, SW1.1
unnamed: D1.2 (A), R1.1
unnamed: D2.1 (K), R14.1
unnamed: D3.2 (A), R15.1
unnamed: D4.1 (K), R45.1
unnamed: P5.1, R26.1, R27.1, R28.1
unnamed: P5.2, R29.1, R30.1, R31.1
unnamed: P5.3, R32.1, R33.1
unnamed: P5.13, R34.1
unnamed: P5.14, R35.1
unnamed: P9.1, U8.6 (R_IN)
unnamed: P9.2, U8.4 (R_IN)
unnamed: P9.3, U8.11 (T_OUT)
unnamed: P9.4, U8.9 (T_OUT)
unnamed: P9.6, U8.7 (R_IN)
unnamed: P9.7, U8.10 (T_OUT)
unnamed: P9.8, U8.5 (R_IN)
unnamed: R3.1, U2.12 (VS2)
unnamed: R4.1, U2.11 (VS1)
unnamed: R5.1, U2.10 (VS0)
VAA: C9.1, C12.1, C13.1, C15.1, C18.1, C21.1, C22.1, C24.1, C25.1, C27.1, C28.1, C30.1, C31.1, C33.1, C34.1, C36.1, C37.1, C38.1, C49.1, C52.1, C53.1, C55.1, C57.1, C60.1, C61.1, C63.1, C64.1, C66.1, C67.1, C68.1, C69.1, C70.1, C72.1, C73.1, C74.1, C75.1, C76.1, C78.1, C84.1, C86.1, C88.1, C89.1, C90.1, C91.1, C92.1, CON3.4 (VDD), CON4.4 (VDD), D2.2 (A), D4.2 (A), P1.4, P4.1, P6.17, P7.13, P11.28, R7.2, R9.2, R10.2, R11.2, R12.2, R16.1, R19.2, R22.2, R24.2, R36.1, R39.1, R42.1, R44.1, R46.1, R49.2, R51.1, R52.1, R54.1, R55.1, R57.1, R58.1, R60.1, R61.1, U1.9 (VCCIO1A), U1.23 (VCCIO1B), U1.31 (VCCIO2), U1.40 (VCCIO3), U1.49 (VCCIO3), U1.67 (VCCIO4), U1.82 (VCCIO5)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

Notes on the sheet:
What're these for?
